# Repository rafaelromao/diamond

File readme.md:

# Diamond

## A 24 keys handwired split keyboard.

Diamond is a handwired board originally designed by me but heavily inspired by the [Rommana](https://github.com/AlaaSaadAbdo/Rommana) and using the switch holders from the [Dactyl Cygnus](https://github.com/juhakaup/keyboards).
- It contains 24 keys only, in the format 1333+2.
- It should be handwired, ideally using single switch PCBs.
- The MCU, reset button and on/off switch goes in the base, below a cover used to hide them.
- These components should be mounted upside down, under this cover.
- The cables for column and rows will pass through holes or cutouts in the cover and can be tightened in the end of assembling to make them less visible in the final build. 

# Diamond Builds

## [Diamond](builds/diamond/diamond.md)

## [Wired Diamond](builds/wired_diamond/wired_diamond.md)

## [Choc Diamond](builds/choc_diamond/choc_diamond.md)

# STL Files

The STL files are provided for the right side only. To print the left side you will have to mirror them.

- [Base Right](stls/v2/base_right.stl)
- [Cover Right](stls/v2/cover_right.stl)
- [Cover Right with Cutout](stls/v2/cover_right_with_cutout.stl)
- [MX Body Right](stls/v2/body_right.stl)
- [MX Body Right - Tilted Thumbs](stls/v2/body_right_tilted.stl)
- [Choc Body Right](stls/v2/choc_body_right.stl)
- [Choc Body Right - Tilted Thumbs](stls/v2/choc_body_right_tilted.stl)

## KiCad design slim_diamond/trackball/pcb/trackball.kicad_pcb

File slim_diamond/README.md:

# Slim Diamond

A wireless Choc v1 Diamond: the Diamond's 1333+2 layout on one reversible
PCB per half, a XIAO-sized nRF52840 module, and a 7 × 20 × 40 mm (500 mAh) battery in
each half. The halves join magnetically into a unibody, or stack back to back for
transport.

## One board, either module

The board takes a Seeed XIAO nRF52840 (the genuine one) or a NologoTech Super52840
(also sold as "MINI NRF52840", "NRF52840 RE:1.4"). Both have the same 14 edge pins
on the same nRF52840 pins, so the firmware is the same; they differ underneath,
where the board reaches the battery, the 12th key and reset:

- **Battery.** Their battery pads are in the same two spots, but swapped: the XIAO's
  + (VBAT) is the pad nearer the module's middle, the Super52840's + (B+) the one
  nearer the USB end. A **battery selector** on the switch face picks which hole is
  +: bridge the row labelled `+MID` for a XIAO, `+USB` for a Super52840. Never both:
  that shorts the battery.
- **12th key (P0.09).** The XIAO's NFC1 pad, or the Super52840's P0.09 pad in its row
  of nine extra GPIO pads: a hole under each, on the same net. Under a XIAO, the
  Super52840's hole touches its NFC2 pad (P0.10), which is unused and idle.
- **Reset** is in the same place on both.
- The Super52840's USB-C legs come through its board: the PCB has clearance holes
  under them, and its USB-C sticks out 0.8 mm further, which the case's recess takes.

The Super52840's pads were measured from several photos, beside a ruler, against the
2.54 mm pin pitch. Its USB-C sits 0.3 to 0.6 mm off centre, towards the D0–D6 pins, so
the leg clearance holes, the notch in the board edge and the case's recess all allow
for that either way (its RST, GND and SWD pads land within 0.2 mm of the XIAO's). The
battery holes are small and sit inside both modules' pads, at least 0.25 mm from the
Super52840's GPIO row under the other half's module, wherever between the two photos'
readings that row really is.

| | |
|---|---|
| Keys | 24 (12 per half): 3×3, one pinky key, two thumbs, all 1u Choc |
| Key layout | The Diamond's angles and stagger (from `body_right.stl`), packed at Choc spacing (18 × 17 mm) |
| PCB | 87.6 × 92.3 mm, 2 layers, 1.6 mm, reversible: one design, order 5. Same cut-diamond outline, so two boards side by side form the diamond. A notch in the edge in front of the USB-C lets a cable's overmold reach the port |
| Wiring | Diodeless, one pin per key (11 Xiao pins + NFC1) |
| Case | Solid base, a pocket per part (0.6 mm clearance), 0.5 mm around the PCB and plate (0.3 at the seam), 93 × 100.5 mm per half at the girdle (the rim is 91.6 × 96.5), with a 45° chamfer under it; tent 6.6°; 20.4 mm at the seam, 10.5 mm at the outer edge (plate included, keycaps excluded). Five pad slots under the floor (below) |
| Anti-slip pads | 5 × 8×2 mm silicone bump-ons per half, as on the original Diamond's base: each slot under the floor (8.6 mm wide, 1.1 deep) holds two pad spots, 8.7 mm apart. Each half sticks its pad in a different end, so stacked, each pad drops into the other half's empty end and the floors (and magnets) still meet. Every key centre sits at least 2.8 mm inside each half's pads, so a press on a border key can't tip it |
| Top plate | Covers the whole board: 1.2 mm Choc v1 plate, 1.0 mm over the PCB (the flange sits 2.2 mm up), 14.0 mm cutouts (`cut_tol` 0.1 per side), a 0.5 mm pocket over the Xiao area for solder blobs, a pocket and cone over the reset button, support pillars, countersunk screw bosses, chamfered bottom edge |
| Power | XIAO nRF52840 or Super52840, 500 mAh 1S LiPo (nominal 7 × 20 × 40 mm) on a JST PH 2.0 socket, MSK-12C02 power switch next to the USB port on the lower outer facet. The wall has a recess the size of a USB-C overmold (14.6 × 7.4 mm, rounded corners, room for a module whose port sits off centre) in front of the port, and a slot open to the top for the lever, widening outwards for a fingernail, with a rounded floor |
| Reset | A 5.1 × 5.1 × 2.0 mm SMD tact switch (TS-1187A) on the switch face, in the nook between the index finger's bottom key and the thumbs, 7.6 mm from the nearest keycap. It reaches through a 45° cone in the plate (4.2 mm across at the top, 2.8 at the throat) with its plunger 0.2 mm under the plate's top: a fingertip presses it, keycaps and palms don't. Press once to reboot, twice for the bootloader, with the case closed |
| Screws | 4 × M3 × 8 flat head (90° countersunk) per half: through the plate and PCB, self-tapping into the solid Nylon base (2.5 mm pilot). `SCREW` in `design.py` switches to heat-set inserts |
| Magnets | One part everywhere: 8 × 1.5 mm N52 discs. Each half has 13: 4 original stacking positions, 3 stand contacts on a circle around the estimated centre of gravity, and 6 evenly spread across the inner wall at 17.8 mm pitch. Every pocket keeps 0.5 mm of plastic all round |
| Assembly | Iron only: no reflow-only parts |

The 500 mAh bay moves the battery away from the inner seam and raises the PCB **1.8 mm**,
keeping the existing 6.6° tent, PCB outline, connector and screw-hole positions. The nominal
7 × 20 × 40 mm finished pack is checked with a 7.5 × 20.5 × 41 mm envelope and the case's
clearance. Measure the actual protected pack, including tabs and wire exit, before printing;
never compress a pouch cell to make it fit. The electrical board and pin map are unchanged.
The trackball and trackpad use smaller 752025, 250 mAh batteries.

Use the half cases, dock and module parts from the same version together: their front facets and
heights are matched.

## Independent tenting on the Ugreen's tilting platform

Each half has three extra floor magnets on a **44 mm circle**, spaced **120° apart** around
the estimated assembled centre of gravity. The pattern is derived from a mass-weighted model
of the nylon case, PCB, battery, switches and magnets, checked by `stand_mount.py`; it is not
a measured balance point. Add three mates of the same **8 × 1.5 mm** size
to the **tilting phone platform**, not the stand's base, with opposite poles facing the half.
For both halves independently, use two stands and six platform magnets. Glue the mates
while aligned with their own half; the right pattern is mirrored. The stand magnets stand
1.5 mm above the platform, so the keyboard's bump-ons remain **0.6 mm clear** and cannot rock it.
The estimated gravity projection remains inside the three-contact triangle through 35° of tilt;
this does not certify the magnets' holding force or the stand's own stability.

`python3 stand_mount.py` checks the group and writes 1:1 templates:
[left](case/stand_magnet_template_left.svg), [right](case/stand_magnet_template_right.svg).
Print at 100%: the dashed contact boundary is **54 mm** across; the magnet-centre circle is 44 mm.
That is the required clear flat
patch, **not a confirmed Ugreen measurement**. Measure the real platform, including rubber,
lips and obstructions, before gluing. Magnet holding force, adhesive strength and stability at
the chosen tilt need a physical load test. The render uses an illustrative stand/platform.

## Before ordering

The board is made in one batch, so check what software can't:

1. **Print** `fab/print_1to1_F_face.pdf` and `fab/print_1to1_B_face.pdf` at 100 % ("Actual
   size", no fit to page). The board outline must measure 87.55 mm across.
2. **Lay the real parts on the prints**, each on the face it's soldered to. The module's
   castellations go over the edge pads, with its USB-C at the board edge. A Choc switch's pins and
   pegs go over one key's holes, and its hot-swap socket over the socket pads on the other face.
   Then the JST socket, the MSK-12C02 (its two pegs in the small holes) and the reset button.
3. **Super52840:** on the print, its B+ and B- pads must cover the two holes in the battery box,
   its `009` pad the round hole in the P0.09 box, and its USB-C legs land inside the two pairs of
   slots. Measure its height from its underside to the top of its USB-C shell: the case allows
   4.3 mm (the XIAO's).
4. **Firmware:** rebuild it before flashing (`b slim_diamond -c` in rafaelromao/keyboards, branch
   `slim-diamond`). `check_pcb.py` confirms that branch lists the board's pins, given the shield's
   `slim_diamond_peripheral_left.overlay` and `_right.overlay` copied to `.render/fw_left.overlay`
   and `.render/fw_right.overlay`.

Checked by the scripts: JLCPCB's limits in the DRC (`pcb/slim_diamond.kicad_dru`: annular ring
0.18, pad holes 0.45 apart, tracks and clearance 0.10, silkscreen 1.0 mm text with a 0.15 stroke),
no tracks under the module's antenna, every net against its intent and the firmware's pin lists
(`check_pcb.py`), both modules' underside pads against the board's copper, and every part, plug,
screw, magnet and pad against the case (`check_fit.py`).

## Files

| Path | What |
|---|---|
| `fab/slim_diamond_jlcpcb.zip` | Gerbers + drill files: upload to JLCPCB as they are |
| `fab/print_1to1_F_face.pdf`, `fab/print_1to1_B_face.pdf` | Both faces at full size, to lay the real parts on before ordering |
| `pcb/` | The KiCad 9 project, its footprint library, 3D stand-ins, and DRC rules |
| `case/case_left.stl`, `case/case_right.stl` | The printed base |
| `case/plate_left.stl`, `case/plate_right.stl` | The printed top plate, oriented top face down for printing |
| `case/dock.stl`, `case/insert.stl` | The cyberdeck dock, and the placeholder for its drawer (below) |
| `stand_mount.py`, `case/stand_magnet_template_*.svg` | Independent-stand contact check and 1:1 platform-magnet templates |
| `trackball/`, `trackpad/` | The drawer modules: scripts, `case/` STLs; the trackball's board in `pcb/` and `fab/` |
| `zmk/` | The modules' ZMK shields |
| `renders/` | Board, board with parts, case, full build; `all.png` has every view on one sheet |
| `BOM.md` | Parts list (AliExpress search terms) |
| `BUILD.md` | Hand-soldering and assembly guide, testing, printing |
| `build-log.html` | The project on one page: both boards, the renders, the BOM and the build guide (open it via raw.githack or GitHub Pages: GitHub shows .html as source) |
| `design.png` | Top view of the placement: sockets (red), Xiao, battery, JST, magnets, screws, the reset button (red, its cone white), pad slots (grey: left pads filled, the right half's dashed) |
| `renders/pads.png` | Both floors from below: where each half's pads go |
| `*.py`, `*.sh` | The generators: everything above is built from them |

## Renders

| Board, top | Board, bottom |
|---|---|
|  |  |
| **Left half with parts, top** | **Left half with parts, bottom** |
|  |  |
| **Case** | **Full build, side (the tent)** |
|  |  |
| **Top plate** | **Top plate, underside** |
|  |  |
| **Joined as a unibody** | **Joined, from above** |
|  |  |
| **Stacked back to back** | **Stacked, side** |
|  |  |

## Cyberdeck dock

A phone on a Ugreen folding stand (base 85 × 105 × 4 mm) is the computer and the screen;
`dock.py` makes one printed part, `case/dock.stl`, that holds both halves around it. Without the
stand it is a tented, splayed unibody, sturdier than the magnets at the seam alone.

- **Over the stand's base**, in a pocket in its underside: the base keeps its own feet on the
  desk and carries the phone. Behind the spine the base is left bare, its hinge (`HINGE`,
  30 × 28 mm, estimated from photos: measure yours) 0.5 mm (`HINGE_CLR`) off the halves, the
  wings and the spine, as far forward as their back corners let it. The pocket's fit holds the
  dock on the base, together with three pairs of the common **8 × 1.5 mm magnets**: three pressed
  into the pocket's roof and three glued on the aluminium base. The tent also keeps room for
  both discs and their backing below the drawer floor.
- **The board's lower half:** under each half's girdle, its widest line, every wall of the dock
  carries on the case's own 45° bottom chamfer down to the desk, one flat plane with it, front,
  back and sides, wings and spine alike. Each wall is built as a plane through its girdle edge, so
  none can fold. Below the girdle the spine and the wings are one piece; above it the spine stops
  0.2 mm short of the seam walls. The wing ends just short of the outer pad, which stands on the
  desk, and each pad recess is shaped to its bump-on's dome so none breaks out of a wall.
- **The halves on wings** the shape of their floors, inner side up, outer pad on the desk, splayed
  12° (`SPLAY`). The extra tent is the least that keeps 1.6 mm of plastic over the base and room
  under the magnets: 5.70°, about 12.3° in all. Every pad slot has a recess, both ends.
- **A spine** between the halves, level with their seam walls' top edges, its front and back
  carrying on both halves' walls, its point cut to a flat as wide as the joined board's front
  flat (about 20 mm). Its middle is a **drawer** (`DRAWER`), pulled out through the front, for a module
  (below) or the **placeholder** (`insert.py`, `case/insert.stl`): a solid block with the modules'
  outline and magnets, flush with the halves, the joined board's diamond cut into its top. The
  drawer is open at both the top and the front. Its sides are straight and uninterrupted: no
  raised ends at the mouth, no ribs or matching grooves. The insert's front is shaped in 3D by
  the halves' exact front facet planes, rather than set back to a vertical wall, so the assembled
  front reads as one element. To take one out, push the tip of its rear hood forwards through the
  rear passage, then pull it out of the front. Lifting is not necessary.
- **Six side magnets per half:** the dock's continuous walls are 2.4 mm thick at their
  thinnest and house six of the common **8 × 1.5 mm N52 magnets per side**, matching all six
  half seam magnets. The gap between the halves is widened by 1.25 mm to preserve insert space.
  Load them from outside, flush, and glue them in; a verified **0.6 mm inner skin** retains them
  inside. Each faces the keyboard half directly outside and the insert's own matching magnet
  through the inner wall at three of those positions. The insert still has only three side
  magnets per side, evenly spaced at y = -7.0, 28.6 and 64.2 mm (seam magnets 2, 4 and
  6, every other magnet in the six-position row). The same insert magnets meet either half directly on the desk.
  Check magnetic holding force with real magnets before relying on it to carry the assembly.
- **A magnet under each pointing module:** one more 8 × 1.5 mm N52 disc in the module's floor and its
  mate in the drawer floor, on the centreline at y = −48.3 mm. Only three underside stand contacts are used, so at least 1 mm of plastic remains between opposing pocket envelopes, even with each pocket 0.2 mm off.
  The rear stays free for USB-C and the power switch.
- **Lap use:** the rear hood recess and USB passage remove material from the dock spine, and an
  insert is not bonded to it. Test a printed dock under load before relying on it for lap use.
- **Magnets in the wings** under six of each half's seven floor magnets. `MAG_COST` rejects
  positions that would add more than 1° to the tent needed for the base pocket. `MAG_ROOF`
  keeps 1 mm under a pocket over the base. Pockets near a 45° wall are nudged inwards to retain
  their surrounding plastic without losing alignment with the case's magnet.
- **Feet:** the underside is cut 0.5 mm (`FOOT_LIFT`) off the desk, and three 8 × 2 mm bump-ons
  under each wing, spread to the largest triangle, make that up.
- 199.0 × 111.3 × 29.8 mm, about 83 cm³. `python3 dock.py` prints the fit check: each half, its pads, the
  base and the hinge against the dock, all 0 mm³, and the plastic round every magnet and foot.

| **With the phone** | **From the front** |
|---|---|
|  |  |
| **Without the stand: a unibody** | **From the side** |
|  |  |
| **The dock** | **Underneath** |
|  |  |

## Drawer modules: a trackball or a trackpad

Two standalone ZMK pointing devices. Either slides into the dock's drawer from the front, or snaps onto
either half's inner wall on the desk, or sits on its own on its bump-ons. They are built like a half: a
tray, a lid, and the same M3 × 8 flat-head screws from the top. The tray is one print, shared by every
module; only the lid changes.

- **Shared by both:** the tray, the main board (keys, hot-swap sockets, power switch), a controller on its own small board,
  a 752025 (250 mAh) battery, and a sensor board holding the reset button. All in the same places, so the
  power slider, the USB-C port and the reset hole are in the same spot on every module.
- **Retention:** three common magnets a side where the halves' inner-wall magnets are (the 2nd, 4th and
  6th), at the same height over the plane both stand on, plus one in the floor over its mate in the drawer.

| **Trackball** | **The parts** |
|---|---|
|  |  |
| **Choc v1 lid, same tray and boards** | **Inside (cut through the middle)** |
|  |  |
| **On a half, on the desk** | **Its boards (front / back)** |
|  |   |
| **Trackpad** | **The parts** |
|  |  |
| **On a half, on the desk** | **The placeholder in the drawer** |
|  |  |

### USB-C

The USB-C port is flush with the module's back, under the power slider, with no wall or floor beneath it,
so a plug goes straight in. The dock has a **12.8 mm wide rear passage all the way down through the
underside**: the nominal model allows a 12.35 × 6.5 mm overmold; check the actual plug and print. At the rear the module's top
extends over the dock's sloped support: the common underside and its mating support are 45°, with 0.4 mm
clearance.

| Trackball: rear connection | Cutaway to the receptacle |
|---|---|
|  |  |
| Trackpad: rear connection | Cutaway to the receptacle |
|  |  |
| Trackball docked | Trackpad docked |
|  |  |

### Slim Diamond Trackball (`trackball/trackball.py`)

A 34 mm ball and two MX or Choc v1 hot-swap keys on one shared PCB. The MX lid stands 4 mm over the
halves; the Choc lid 1.2 mm. Their front and side upper facets run from the halves' top height to the lid top. The front facet is steeper to preserve the 40 mm trackpad rim and key/power-switch clearance; the lower front remains matched to the drawer.

- The ball sits in a cup in the lid on three 3 mm Si3N4 balls and lifts straight out. Under it, a PMW3610
  on its own board looks up through an LM18-LSI lens (circuit after siderakb's pmw3610-pcb, CERN-OHL-P-2.0,
  at 3.3 V logic with a TLV74318).
- The main board accepts **MX or Choc v1 hot-swap sockets**, not both populated together. Choc sockets
  face 180° opposite the MX sockets. MX uses `trackball/case/lid.stl` (1.5 mm plate), Choc uses
  `trackball/case/lid_choc.stl` (1.2 mm plate). Choc v2 is not supported.
- The controller stands face down on a standard 2.54 mm header on its own small board, its USB-C port
  flush with the back wall. That board drops into the tray between printed stops, which take a plug's force.
- Eight 15 mm stacking pins join the controller board to the main board, beside the controller, and the battery and reset
  come by wire from the controller's own pads to `VBAT` and `R2`. The main board does not lift out once they are soldered.
  The sensor's SCLK, SDIO (3-wire SPI), NCS and MOTION go to pads `CK`, `IO`, `CS` and `MO`. Each pad takes one
  controller pin, on both modules; the table is in `BUILD.md`, and in `trackball/controller_pinout.py`.
- One panel to order (`trackball/fab/trackball_jlcpcb.zip`), 53.7 × 99.5 mm: the main board and the
  sensor board at opposite ends of a long bridge, with a row of snap holes at each end, and the
  controller board on a short tab off the sensor board's side.
  `trackball/route.sh` builds, routes and checks it (`build_pcb.py`, Freerouting, DRC).
- **One orderable panel for nice!nano v2 or plain XIAO nRF52840:** both stand on the same header. Rows 5 to 7 are
  GPIOs on both, so the signals differ only in firmware. One solder jumper chooses the 3.3 V pin:
  a nice!nano has VCC in row 4 where a XIAO has 3V3 in row 3. Its pin rows sit 0.2 mm further back than a
  nice!nano's, so a XIAO's USB-C mouth lies 0.2 mm inside the rear plane. The tray's seats and stops clear the
  Seeed STEP reference, but actual revisions, clones, wiring and retention still need checking.
- The sensor's posts print 0.4 mm low. Equal shims can adjust the optical gap, but the real ball-to-board
  distance and lens reference-plane height must be measured; see `BUILD.md` for the calculation and limits.

### Slim Diamond Trackpad (`trackpad/trackpad.py`)

The same module with a 40 mm Cirque (TM040040, I²C) in the lid instead of the ball. It uses the Choc
sockets on the shared main board and stands at the Choc lid's height, 1.2 mm over the halves.

- Retain the supplied I²C breakout with its pull-up resistors and original 12-pin flat cable.
  Four wires connect the MCU to the breakout; one separate DR wire connects the MCU directly to the
  Cirque underside. The sensor/reset board area reserves a 24 × 18 × 4.5 mm breakout envelope on a
  2.5 mm insulating spacer, plus cable-bend room, with no printed holder. Verify actual kit dimensions.

| Wire | nice!nano v2 | Plain XIAO nRF52840 |
|---|---|---|
| Breakout SDA, on pad `IO` | D3 (P0.20) | D5 (P0.05) |
| Breakout SCL, on pad `CK` | D2 (P0.17) | D4 (P0.04) |
| Cirque DR, separate underside wire, on pad `MO` | D4 (P0.22) | D6 (P1.11) |
| Breakout GND, VDD | GND, VCC (3.3 V) | GND, 3V3 |
| Main board K1, K2 | D19 (P0.02), D21 (P0.31) | D7 (P1.12), D9 (P1.14) |
| Main board `G`, by stacking pin | GND | GND |
| Main board `VBAT`, `R2`, by wire | B+, RST | BAT+, reset pad |

Use I²C at address `0x2A`; confirm R1 is absent on an SPI-labelled kit and leave R7/R8 fitted for
3.3 V operation.

**Firmware** (`zmk/`): a ZMK config with both shields, `slim_diamond_trackball` (the PMW3610 through
badjeff's zmk-pmw3610-driver) and `slim_diamond_trackpad` (the Cirque through Zephyr's in-tree
Pinnacle driver), pinned in `zmk/config/west.yml`. Key 1 clicks left; key 2 clicks right, and
held turns pointing into scrolling; both together click middle. If the pointer runs the wrong way,
check the selected driver's orientation settings against its binding before changing the overlay.

`python3 -m unittest test_stl_export test_half_battery test_drawer test_module_assembly test_xiao_option trackball.test_layout`
runs the checks.

For the XIAO shields, initialize a west workspace from `zmk/config/west.yml`, then build ZMK's `app`
for `xiao_ble//zmk` with `SHIELD=slim_diamond_trackball_xiao` or `slim_diamond_trackpad_xiao` and
`ZMK_EXTRA_MODULES` set to this directory's absolute `zmk/` path. For example, from that workspace:

```sh
west build -s zmk/app -d build-trackball -b xiao_ble//zmk -- -DSHIELD=slim_diamond_trackball_xiao -DZMK_EXTRA_MODULES=/absolute/path/to/slim_diamond/zmk
west build -s zmk/app -d build-trackpad -b xiao_ble//zmk -- -DSHIELD=slim_diamond_trackpad_xiao -DZMK_EXTRA_MODULES=/absolute/path/to/slim_diamond/zmk
```

The generated `zephyr/zmk.uf2` is controller-specific. Compilation is not a physical sensor, charging or Bluetooth test.

## How a reversible board makes two halves

The left half gets its parts on the bottom (B) face. The right half is the same
board turned over, so its parts go on the F face. Silkscreen says which face is
which (`LEFT: parts on this face`).

Turned over, the Xiao's pins land mirrored: where the left half has D0, D1 and D2,
the right half has VBUS, GND and 3V3. Those three pins reach their keys through
solder jumpers. **Bridge the three jumpers on the face without the Xiao** (inside its
outline, labelled D0–D2) and leave the other three open. The other eight edge pins
are GPIO either way. The firmware just lists different pins per half.

Diodeless needs 12 inputs and the Xiao's edge only has 11, so the 12th key uses
the NFC1 pad on the Xiao's underside, through a plated hole you solder from the
other face. NFC itself is not used.

The reset button is wired the same way: the Xiao's reset test pad (pad 17 in
Seeed's footprint, `EN` in their symbol; TP2 on the nRF52840's P0.18/RESET in
Seeed's schematic) is reached through a plated hole filled from the switch face,
and the button joins it to GND. Each half's reset hole has its own net (`RST_L`,
`RST_R`) wired only to that half's button pads: turned over, one half's reset
hole lands under the other half's GND test pad. No pin changes, so the firmware
is unaffected.

Pin map (from `pcb/pinout.json`):

| Key | Left | Right |
|---|---|---|
| pinky | D0 | D0 |
| ring top / home / bottom | D4 / D3 / D1 | D9 / D10 / D1 |
| middle top / home / bottom | D5 / D2 / D6 | D8 / D2 / D7 |
| index top / home / bottom | NFC1 / D7 / D8 | NFC1 / D6 / D5 |
| thumb outer / inner | D9 / D10 | D4 / D3 |

## Firmware

ZMK shield `slim_diamond` in [rafaelromao/keyboards](https://github.com/rafaelromao/keyboards)
(`zmk/keyboards/rafaelromao/slim_diamond`). It builds for `xiao_ble//zmk` with the
same keymap as the other Diamonds:

```sh
b slim_diamond -c   # central left, peripheral left/right, dongle
```

## Regenerating

For a mechanical blind review or print-readiness review, apply [REVIEW_CHECKLIST.md](REVIEW_CHECKLIST.md), including opposing pockets in the populated assembly.

Requires Python 3 with `requirements.txt`, podman (KiCad 9 runs in the
`docker.io/kicad/kicad:9.0` image through `kicad.sh`), and Freerouting 2.x with
Java 25.

```sh
python3 design.py        # placement, tent, outlines, magnets, screws -> design.json, design.png
FREEROUTING=/path/freerouting.jar ./route.sh   # footprints, board, routing, pours, DRC
./fab.sh                 # gerbers and drill files -> fab/slim_diamond_jlcpcb.zip
python3 magnets.py       # only after a layout change: measures the base for the magnets to pin in design.py
python3 case.py          # base and plate STLs (and their 3D models for renders)
python3 check_fit.py     # parts, plate, solder blobs, the reset button and its cone, screws, magnets, pad slots, a USB-C plug and the lever against
                         # the case, the pads stacked, and the pads' balance: all 0 mm³, ALL CLEAR
./kicad.sh python3 check_pcb.py   # every net against its intent, and the firmware's pin lists: ALL CLEAR
python3 dock.py          # the cyberdeck dock's STL, and its fit check: all 0 mm³
python3 trackball/trackball.py && ./trackball/route.sh && ./trackball/fab.sh   # the three-board panel and gerbers
./kicad.sh python3 trackball/check_controller_pcb.py   # every pad, header pin and jumper net
python3 trackpad/trackpad.py                       # trackpad module: case and fit check
python3 insert.py                                  # the drawer's placeholder
python3 vrml.py && python3 scene.py && ./kicad.sh python3 render_boards.py && ./render.sh
python3 page.py          # build-log.html's BOM and build-guide sections, from BOM.md and BUILD.md
```

`layout.py` holds the Diamond geometry. `design.py` places everything else and
holds the tolerances. The outline is the fewest-facet (`GEM_FACETS`) convex
polygon around both halves joined. `XIAO_SPOT` pins the Xiao's position;
set it to `None` to search again, and if the board won't route completely, try
the runners-up the search writes to `xiao_alternatives.json`. `RESET_SPOT` pins the reset button and `BUTTON` holds its datasheet heights
and the plate's pocket and cone; `design.py` asserts its clearances. `PAD_SLOTS` pins the
pad slots the same way (`None` searches again for the slots that keep every key
centre deepest inside both halves' pads). `MAG_FLOOR_SPOTS` and `MAG_SIDE_SPOTS` pin the
magnets, found by `magnets.py` against the solid base around the pads, parts and screws.

Credits: the Choc hot-swap footprint follows [kiswitch](https://github.com/kiswitch/kiswitch)
(MIT). The Xiao pad positions follow Seeed's
[OPL KiCad library](https://github.com/Seeed-Studio/OPL_Kicad_Library). The reset button's pads follow
KiCad's `Button_Switch_SMD:SW_SPST_TL3342` from the
[official footprint library](https://gitlab.com/kicad/libraries/kicad-footprints) (CC-BY-SA 4.0), which
matches XKB's TS-1187A land pattern.

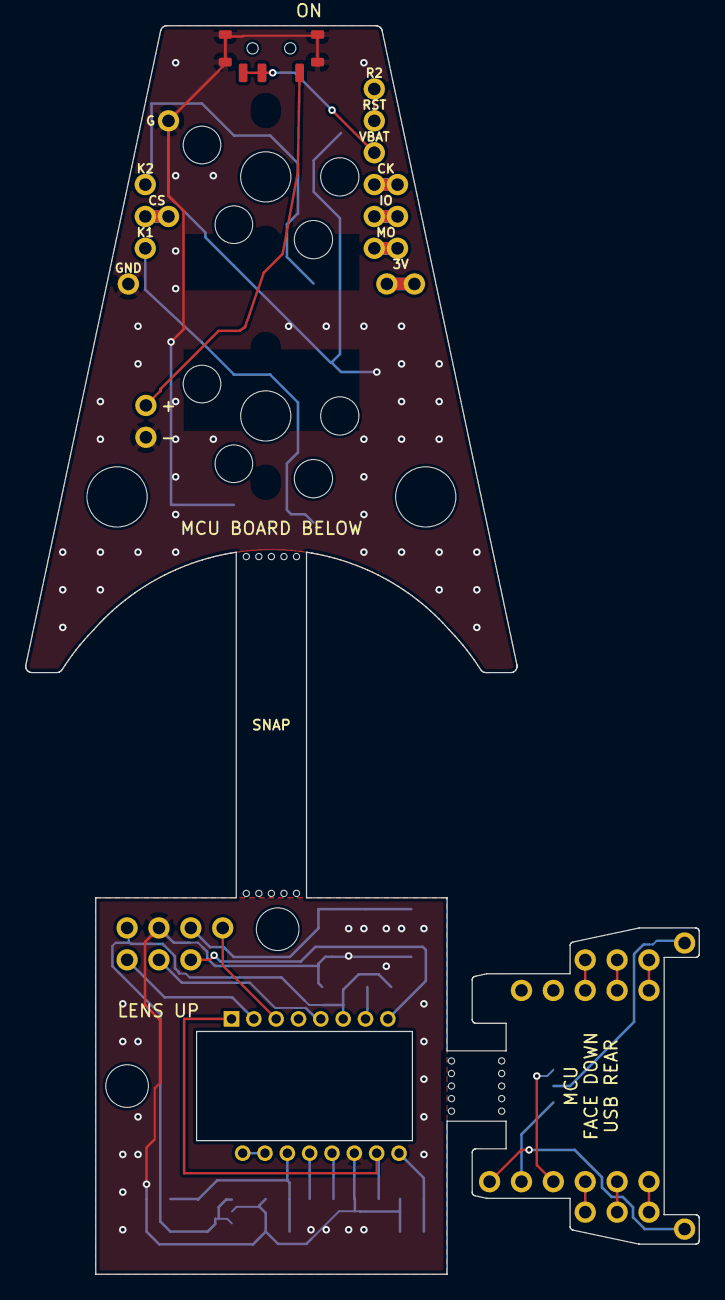
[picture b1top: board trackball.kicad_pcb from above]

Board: 2 copper layers, 53.7 x 99.5 mm, 86 parts (0 on the bottom side), 35 nets.

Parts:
H1, H2: post; PostHole
J1: SCLK; WirePad
J2: SDIO; WirePad
J3: NCS; WirePad
J4: MOTION; WirePad
J5: RST; WirePad
J6: VCC; WirePad
J7, J9: GND; WirePad
J8: BAT+; WirePad
J10: VBAT; WirePad
J11: R2; WirePad
JP1: 3V: XIAO or nice!nano; SolderJumper3_Back
L1: L5; WirePad
L2: L6; WirePad
L3: L7; WirePad
L4: L8; WirePad
L5: R5; WirePad
L6: R6; WirePad
L7: R7; WirePad
L8: R8; WirePad
MB1, MB2, MB3, MB4, MB5, MB6, MB7, MB8, MB9, MB10, MB11, MB12, MB13, MB14, MB15, MB16, MB17, MB18, MB19, MB20: bite; MouseBite
ML1: L5; WirePad
ML2: L6; WirePad
ML3: L7; WirePad
ML4: L8; WirePad
ML5: R5; WirePad
ML6: R6; WirePad
ML7: R7; WirePad
ML8: R8; WirePad
MP1: L2; WirePad
MP2: L3; WirePad
MP3: L4; WirePad
MP4: L5; WirePad
MP5: L6; WirePad
MP6: L7; WirePad
MP7: R3; WirePad
MP8: R4; WirePad
MP9: R5; WirePad
MP10: R6; WirePad
MP11: R7; WirePad
S1: PMW3610DM-SUDU + LM18-LSI; PMW3610_Back
S2: TLV74318PDBVR; SOT-23-5_Back
S3: TS-1187A reset; SW_TS1187A_Back
SC1: 3.3uF; C_0805_Back
SC2, SC3, SC4: 100nF; C_0805_Back
SC5, SC7: 10nF; C_0805_Back
SC6: 10uF; C_0805_Back
SC8, SC9: 1uF; C_0805_Back
SH1, SH2: M3; MountingHole_M3
SJ1: VCC; WirePad
SJ2: GND; WirePad
SJ3: RST; WirePad
SJ4: SCLK; WirePad
SJ5: SDIO; WirePad
SJ6: NCS; WirePad
SJ7: MOTION; WirePad
SR1: 10k; C_0805_Back
SW1: MX / Choc v1 key 1; SW_MX_Choc_V1_Hotswap
SW2: MX / Choc v1 key 2; SW_MX_Choc_V1_Hotswap
SW3: MSK-12C02 power; SW_MSK12C02

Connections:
BAT+: J8.1, SW3.1
GND: J7.1, J9.1, L4.1, SW1.1, SW2.1, SW3.SH
K1: L3.1, SW1.2
K2: L1.1, SW2.2
MOTION: J4.1, L7.1
M_3V: JP1.2, ML8.1
M_CK: ML5.1, MP9.1
M_CS: ML2.1, MP5.1
M_GND: ML4.1, MP1.1
M_IO: ML6.1, MP10.1
M_K1: ML3.1, MP6.1
M_K2: ML1.1, MP4.1
M_L3: JP1.1, MP2.1
M_L4: JP1.3, MP3.1
M_MO: ML7.1, MP11.1
NCS: J3.1, L2.1
RST: J5.1, J11.1
SCLK: J1.1, L5.1
SDIO: J2.1, L6.1
S_CN: S1.13, SC4.2
S_CP: S1.12, SC4.1
S_GND: S1.11, S2.2, S3.2, SC1.2, SC2.2, SC3.2, SC5.2, SC6.2, SC7.2, SC8.2, SC9.2, SJ2.1
S_MOTION: S1.8, SJ7.1
S_NCS: S1.5, SJ6.1
S_NRST_S: S1.7, SR1.2
S_RST: S3.1, SJ3.1
S_SCLK: S1.3, SJ4.1
S_SDIO: S1.2, SJ5.1
S_V1V8: S1.14, S2.5, SC1.1, SC2.1, SC9.1
S_VCC: S1.6, S2.1, S2.3, SC3.1, SC8.1, SJ1.1, SR1.1
S_VCP: S1.9, SC6.1, SC7.1
S_VCSEL: S1.1, S1.10, SC5.1
S_XYL: S1.15, S1.16
VBAT: J10.1, SW3.2, SW3.3
VCC: J6.1, L8.1

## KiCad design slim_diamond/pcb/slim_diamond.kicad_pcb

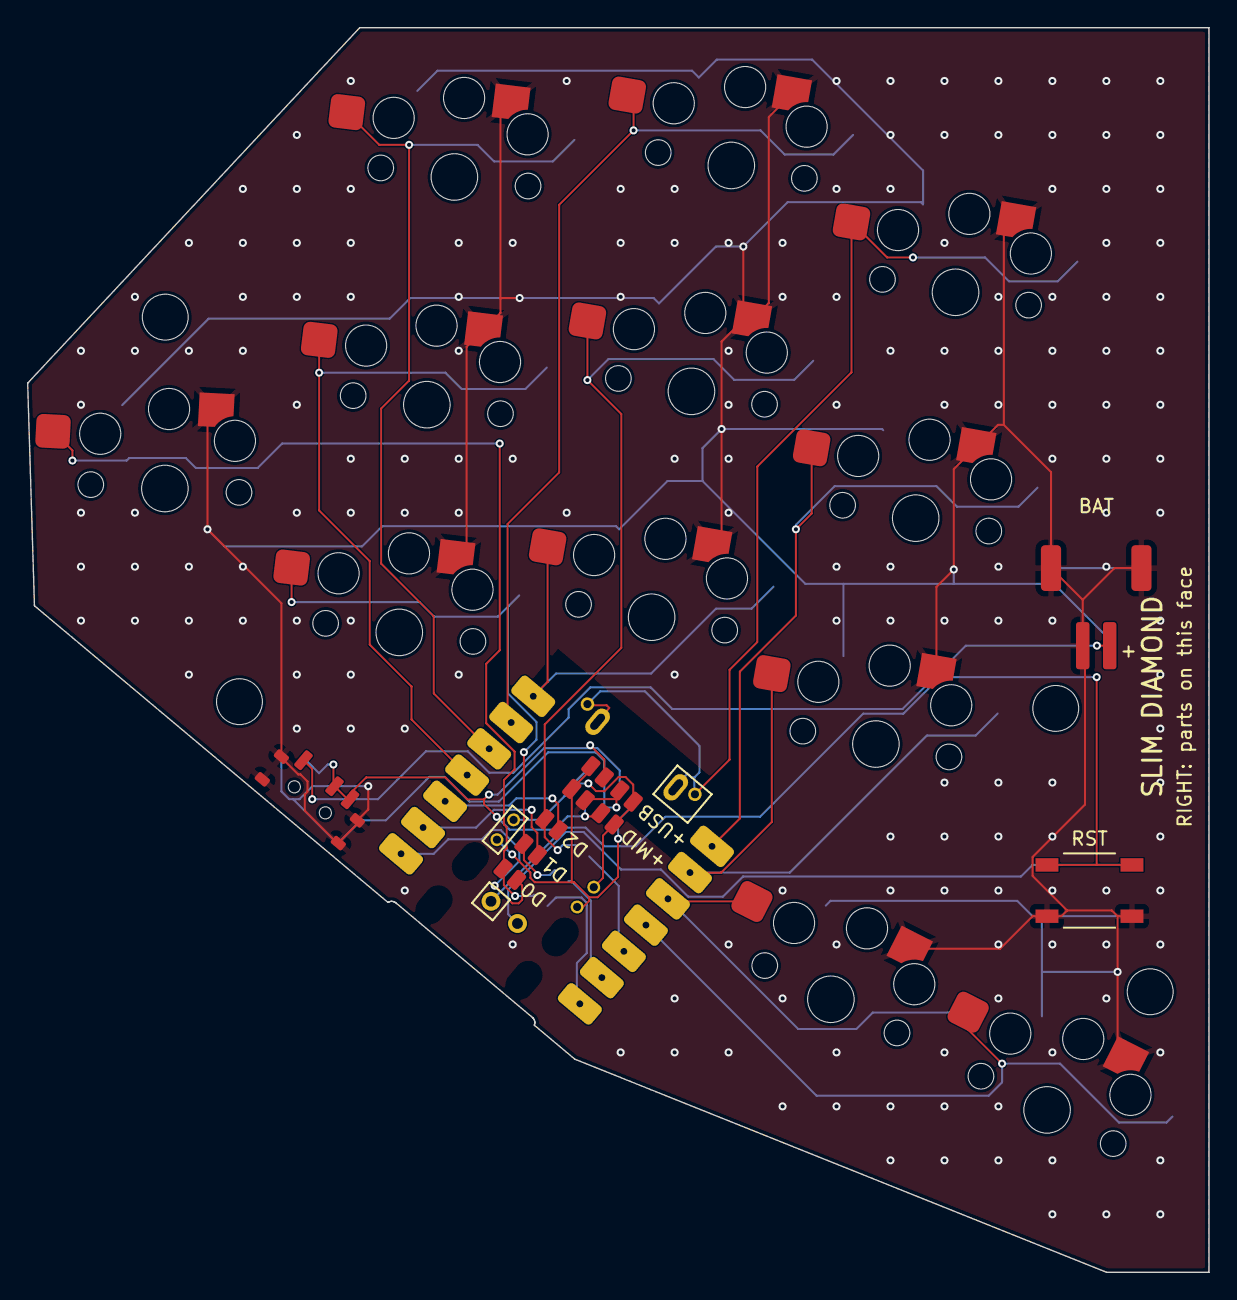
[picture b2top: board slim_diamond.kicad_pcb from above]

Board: 2 copper layers, 87.6 x 92.3 mm, 34 parts (0 on the bottom side), 25 nets.

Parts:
H1, H2, H3, H4: M3; MountingHole_M3
J1: JST PH 2.0 battery; JST_PH_S2B_Reversible
JP1: D0 left; SolderJumper_F
JP2: D1 left; SolderJumper_F
JP3: D2 left; SolderJumper_F
JP12: D2 right; SolderJumper_B
JP13: D1 right; SolderJumper_B
JP14: D0 right; SolderJumper_B
JS1: +MID BATM; SolderJumper_F
JS2: +MID BATU; SolderJumper_F
JS3: +MID BATM; SolderJumper_B
JS4: +MID BATU; SolderJumper_B
JS5: +USB BATM; SolderJumper_F
JS6: +USB BATU; SolderJumper_F
JS7: +USB BATM; SolderJumper_B
JS8: +USB BATU; SolderJumper_B
SW1: pinky; SW_Choc_V1_Hotswap_Reversible
SW2: ring_top; SW_Choc_V1_Hotswap_Reversible
SW3: ring_home; SW_Choc_V1_Hotswap_Reversible
SW4: ring_bottom; SW_Choc_V1_Hotswap_Reversible
SW5: middle_top; SW_Choc_V1_Hotswap_Reversible
SW6: middle_home; SW_Choc_V1_Hotswap_Reversible
SW7: middle_bottom; SW_Choc_V1_Hotswap_Reversible
SW8: index_top; SW_Choc_V1_Hotswap_Reversible
SW9: index_home; SW_Choc_V1_Hotswap_Reversible
SW10: index_bottom; SW_Choc_V1_Hotswap_Reversible
SW11: thumb_outer; SW_Choc_V1_Hotswap_Reversible
SW12: thumb_inner; SW_Choc_V1_Hotswap_Reversible
SW13: MSK-12C02; SW_MSK12C02_Reversible
SW14: TS-1187A reset; SW_TS1187A_Reversible
U1: XIAO nRF52840 / Super52840; nRF52840_Module_Reversible

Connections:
BAT+: J1.1, SW13.1
BATM: JS1.1, JS3.2, JS5.1, JS7.2, U1.BATM
BATU: JS2.2, JS4.1, JS6.2, JS8.1, U1.BATU
GND: J1.2, J1.MP, JS2.1, JS4.2, JS5.2, JS7.1, SW1.1, SW2.1, SW3.1, SW4.1, SW5.1, SW6.1, SW7.1, SW8.1, SW9.1, SW10.1, SW11.1, SW12.1, SW13.SH, SW14.2, SW14.4
K_index_bottom: SW10.2, U1.L9
K_index_home: SW9.2, U1.L8
K_index_top: SW8.2, U1.NFC1
K_middle_bottom: SW7.2, U1.L7
K_middle_home: JP3.2, JP12.2, SW6.2
K_middle_top: SW5.2, U1.L6
K_pinky: JP1.2, JP14.2, SW1.2
K_ring_bottom: JP2.2, JP13.2, SW4.2
K_ring_home: SW3.2, U1.L4
K_ring_top: SW2.2, U1.L5
K_thumb_inner: SW12.2, U1.L11
K_thumb_outer: SW11.2, U1.L10
RST_L: SW14.1, U1.RSTL
RST_R: SW14.3, U1.RSTR
VBAT: JS1.2, JS3.1, JS6.1, JS8.2, SW13.2, SW13.3
X_L1: JP1.1, U1.L1
X_L2: JP2.1, U1.L2
X_L3: JP3.1, U1.L3
X_L12: JP12.1, U1.L12
X_L13: JP13.1, U1.L13
X_L14: JP14.1, U1.L14

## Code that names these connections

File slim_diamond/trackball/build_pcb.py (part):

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D = json.load(open(os.path.join(HERE, "design.json")))

WIRES_MAIN = ["SCLK", "SDIO", "NCS", "MOTION", "RST", "VCC", "GND"]     # in design.json wire_pads order
PAD_LABELS = {"SCLK": "CK", "SDIO": "IO", "NCS": "CS", "MOTION": "MO", "VCC": "3V", "GND": "G"}
WIRES_SENSOR = ["VCC", "GND", "RST", "SCLK", "SDIO", "NCS", "MOTION"]   # trackball.py SENSOR_PARTS J1 order
SENSOR_NETS = {   # PMW3610 pins (siderakb's 3.3 V logic configuration)
    "1": "VCSEL", "10": "VCSEL", "15": "XYL", "16": "XYL", "12": "CP", "13": "CN", "9": "VCP",
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
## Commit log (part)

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2025-03-01 add diamond docs
2025-03-30 add wired and choc diamonds
2025-03-31 update images
2025-04-14 add license
2025-05-30 update build

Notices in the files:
parts and their libraries:
PixArt PMW3610DM-SUDU on the back face, LM18-LSI lens on the front; after siderakb/pmw3610-pcb (CERN-OHL-P-2.0)
